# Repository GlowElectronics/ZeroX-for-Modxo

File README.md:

# ZeroX
ZeroX is an interface between the RP2040 Zero and the original Xbox LPC header.

Designed specifically for the Modxo (Modsho) project from shalxmva (https://github.com/shalxmva/modxo)

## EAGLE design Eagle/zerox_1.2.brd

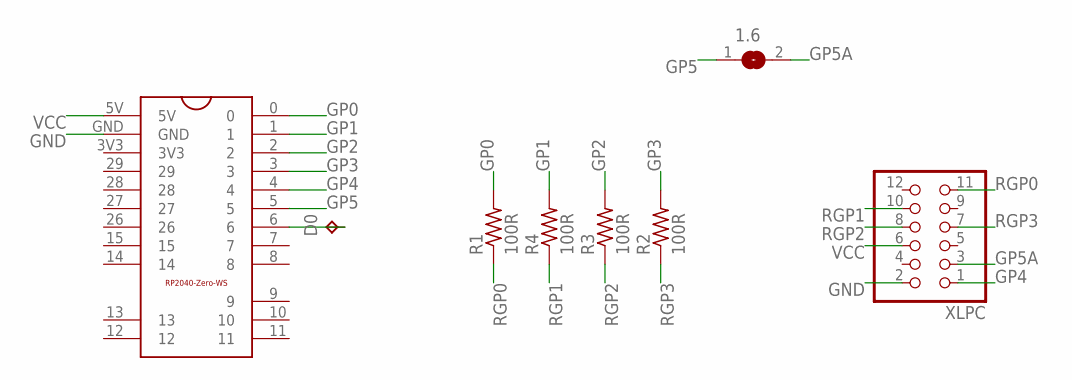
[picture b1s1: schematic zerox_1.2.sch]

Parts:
1.6: SJ
D0: TPTP12SQ; TP12SQ
R1, R2, R3, R4: 100R; R0805
U$1: RPI2040-WS-SMD; RPI2040-WS
XLPC: PINHD-2X6; 2X06

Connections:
GND: U$1.GND, XLPC.2
GP0: R1.2, U$1.0
GP1: R4.2, U$1.1
GP2: R3.2, U$1.2
GP3: R2.2, U$1.3
GP4: U$1.4, XLPC.1
GP5: 1.6.1, U$1.5
GP5A: 1.6.2, XLPC.3
unnamed: D0.TP, U$1.6
RGP0: R1.1, XLPC.11
RGP1: R4.1, XLPC.10
RGP2: R3.1, XLPC.8
RGP3: R2.1, XLPC.7
VCC: U$1.5V, XLPC.6

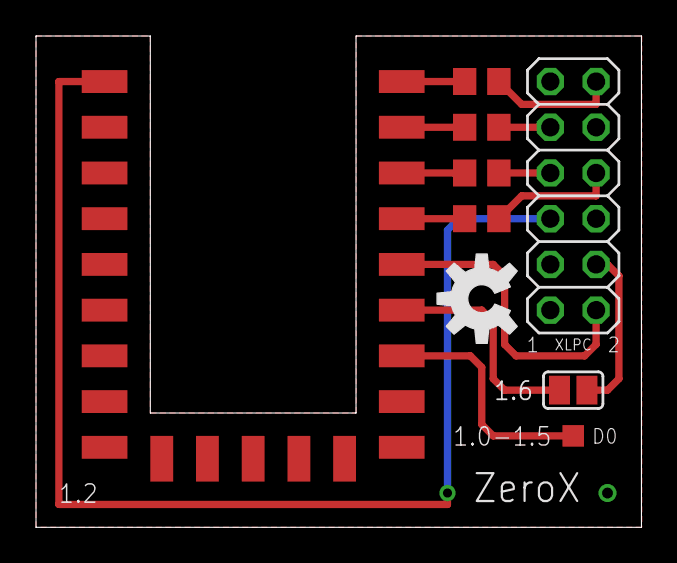
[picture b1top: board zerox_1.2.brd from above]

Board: 2 copper layers, 33.6 x 27.3 mm, 9 parts (0 on the bottom side), 14 nets.

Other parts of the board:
U$2: OSHW-LOGO-M

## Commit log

2024-05-19 Version 1.2

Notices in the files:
parts and their libraries:
SparkFun-Aesthetics: Licensing: Creative Commons ShareAlike 4.0 International - https://creativecommons.org/licenses/by-sa/4.0
